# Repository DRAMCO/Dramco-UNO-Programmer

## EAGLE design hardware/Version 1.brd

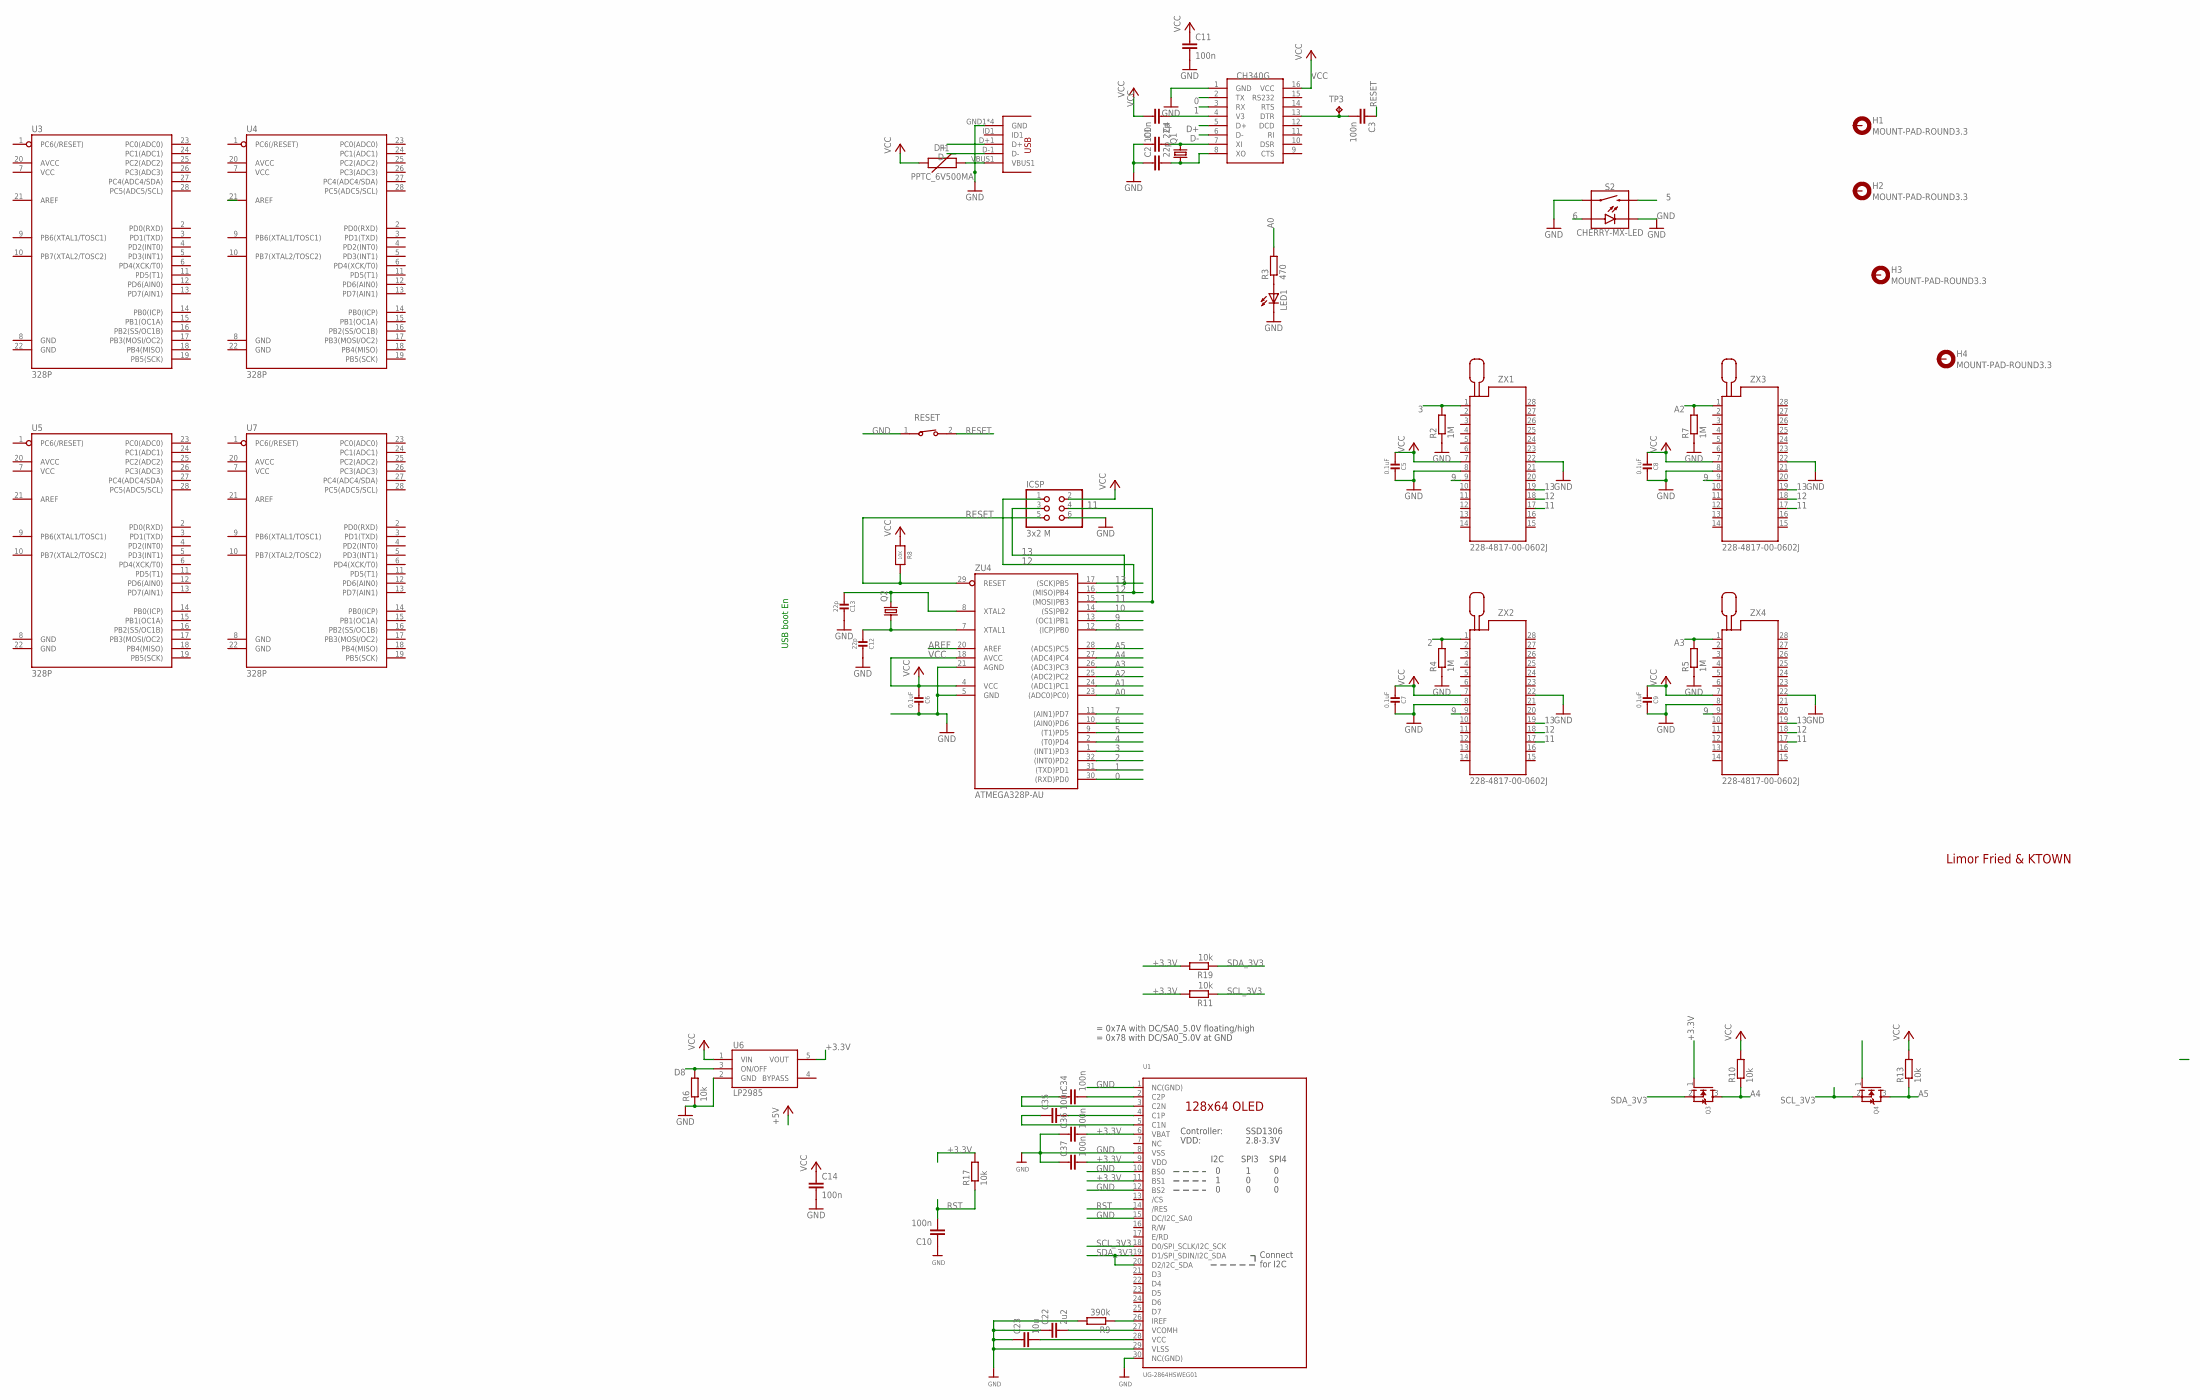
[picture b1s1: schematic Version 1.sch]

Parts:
C1, C2: 22p; C0805
C3, C4, C10, C11, C14, C34, C35, C36, C37: 100n; C0805
C5, C6, C7, C8, C9: 0.1uF; 0805-NO
C12, C13: 22p; 0805_10MGAP
C22: 2u2; C0805
C23: 10u; C0805
F1: PPTC_6V500MA; 0805
H1, H2, H3, H4: MOUNT-PAD-ROUND3.3; 3,3-PAD
ICSP: 3x2 M; 2X03_ROUND_70MIL
J1: USB-AB; USB-AB-MICRO-SMD_V02_BOSS
LED1: LEDCHIPLED_0805; CHIPLED_0805
Q1, Q2: CRYSTALHC49S; HC49/S
Q3, Q4: MOSFET-NREFLOW; SOT23
R2, R4, R5, R7: 1M; R0805
R3: 470; R0805
R6, R10, R11, R13, R17, R19: 10k; R0805
R8: 10K; _0805MP
R9: 390k; R0805
RESET: 434111043826
S2: CHERRY-MX-LED
TP3: TPTP18R; TP18R
U1: UG-2864HSWEG01; UG-2864HSWEG01_0.96IN_WRAPAROUND
U2: CH340G; SOIC16
U3, U4, U5, U7: 328P; DIP28
U6: LP2985AIM5-3.3; SOT25
ZU4: ATMEGA328P-AU; TQFP32-08
ZX1, ZX2, ZX3, ZX4: 228-4817-00-0602J

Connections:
0: U2.2 (TX), ZU4.30 ((RXD)PD0)
1: U2.3 (RX), ZU4.31 ((TXD)PD1)
2: R4.2, ZU4.32 ((INT0)PD2), ZX2.1
3: R2.2, ZU4.1 ((INT1)PD3), ZX1.1
4: ZU4.2 ((T0)PD4)
5: S2.S2, ZU4.9 ((T1)PD5)
6: S2.A, ZU4.10 ((AIN0)PD6)
7: ZU4.11 ((AIN1)PD7)
8: ZU4.12 ((ICP)PB0)
9: ZU4.13 ((OC1)PB1), ZX1.9, ZX2.9, ZX3.9, ZX4.9
10: ZU4.14 ((SS)PB2)
11: ICSP.4, ZU4.15 ((MOSI)PB3), ZX1.17, ZX2.17, ZX3.17, ZX4.17
12: ICSP.1, ZU4.16 ((MISO)PB4), ZX1.18, ZX2.18, ZX3.18, ZX4.18
13: ICSP.3, ZU4.17 ((SCK)PB5), ZX1.19, ZX2.19, ZX3.19, ZX4.19
+3.3V: C36.2, C37.2, Q3.1 (G), Q4.1 (G), R11.2, R17.2, R19.2, U1.6 (VBAT), U1.9 (VDD), U1.11 (BS1), U6.5 (VOUT)
A0: R3.2, ZU4.23 ((ADC0)PC0))
A1: ZU4.24 ((ADC1)PC1)
A2: R7.2, ZU4.25 ((ADC2)PC2), ZX3.1
A3: R5.2, ZU4.26 ((ADC3)PC3), ZX4.1
A4: Q3.3 (D), R10.1, ZU4.27 ((ADC4)PC4)
A5: Q4.3 (D), R13.1, ZU4.28 ((ADC5)PC5)
AREF: ZU4.20 (AREF)
AREF1: U4.21 (AREF)
D8: R6.2, U6.3 (ON/OFF)
D+: J1.D+1 (D+), U2.5 (D+)
D-: J1.D-1 (D-), U2.6 (D-)
GND: C1.1, C2.1, C5.1, C6.1, C7.1, C8.1, C9.1, C10.1, C11.2, C12.1, C13.1, C14.2, C22.1, C23.1, C36.1, C37.1, ICSP.6, J1.GND1 (GND), J1.P$1 (GND), J1.P$2 (GND), J1.P$3 (GND), LED1.C, R2.1, R4.1, R5.1, R6.1, R7.1, R9.2, RESET.1, S2.K (C), S2.S1, U1.1 (NC(GND)), U1.8 (VSS), U1.10 (BS0), U1.12 (BS2), U1.15 (DC/I2C_SA0), U1.29 (VLSS), U1.30 (NC(GND)), U2.1 (GND), U6.2 (GND), ZU4.5 (GND), ZU4.21 (AGND), ZX1.8, ZX1.22, ZX2.8, ZX2.22, ZX3.8, ZX3.22, ZX4.8, ZX4.22
unnamed: C1.2, Q1.2, U2.7 (XI)
unnamed: C23.2, U1.28 (VCC)
unnamed: C2.2, Q1.1, U2.8 (XO)
unnamed: C3.2, TP3.TP, U2.13 (DTR)
unnamed: C4.1, U2.4 (V3)
unnamed: LED1.A, R3.1
unnamed: F1.2, J1.VBUS1
unnamed: C34.2, U1.2 (C2P)
unnamed: C22.2, U1.27 (VCOMH)
unnamed: R9.1, U1.26 (IREF)
unnamed: C34.1, U1.3 (C2N)
unnamed: C35.2, U1.4 (C1P)
unnamed: C35.1, U1.5 (C1N)
RESET: C3.1, ICSP.5, R8.1, RESET.2, ZU4.29 (RESET)
RST: C10.2, R17.1, U1.14 (/RES)
SCL_3V3: Q4.2 (S), R11.1, U1.18 (D0/SPI_SCLK/I2C_SCK)
SDA_3V3: Q3.2 (S), R19.1, U1.19 (D1/SPI_SDIN/I2C_SDA), U1.20 (D2/I2C_SDA)
VCC: C4.2, C5.2, C6.2, C7.2, C8.2, C9.2, C11.1, C14.1, F1.1, ICSP.2, R8.2, R10.2, R13.2, U2.16 (VCC), U6.1 (VIN), ZU4.4 (VCC), ZU4.18 (AVCC), ZX1.7, ZX2.7, ZX3.7, ZX4.7
XTAL1: C12.2, Q2.1, ZU4.7 (XTAL1)
XTAL2: C13.2, Q2.2, ZU4.8 (XTAL2)

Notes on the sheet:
USB boot En
Limor Fried & KTOWN
= 0x7A with DC/SA0_5.0V floating/high
= 0x78 with DC/SA0_5.0V at GND

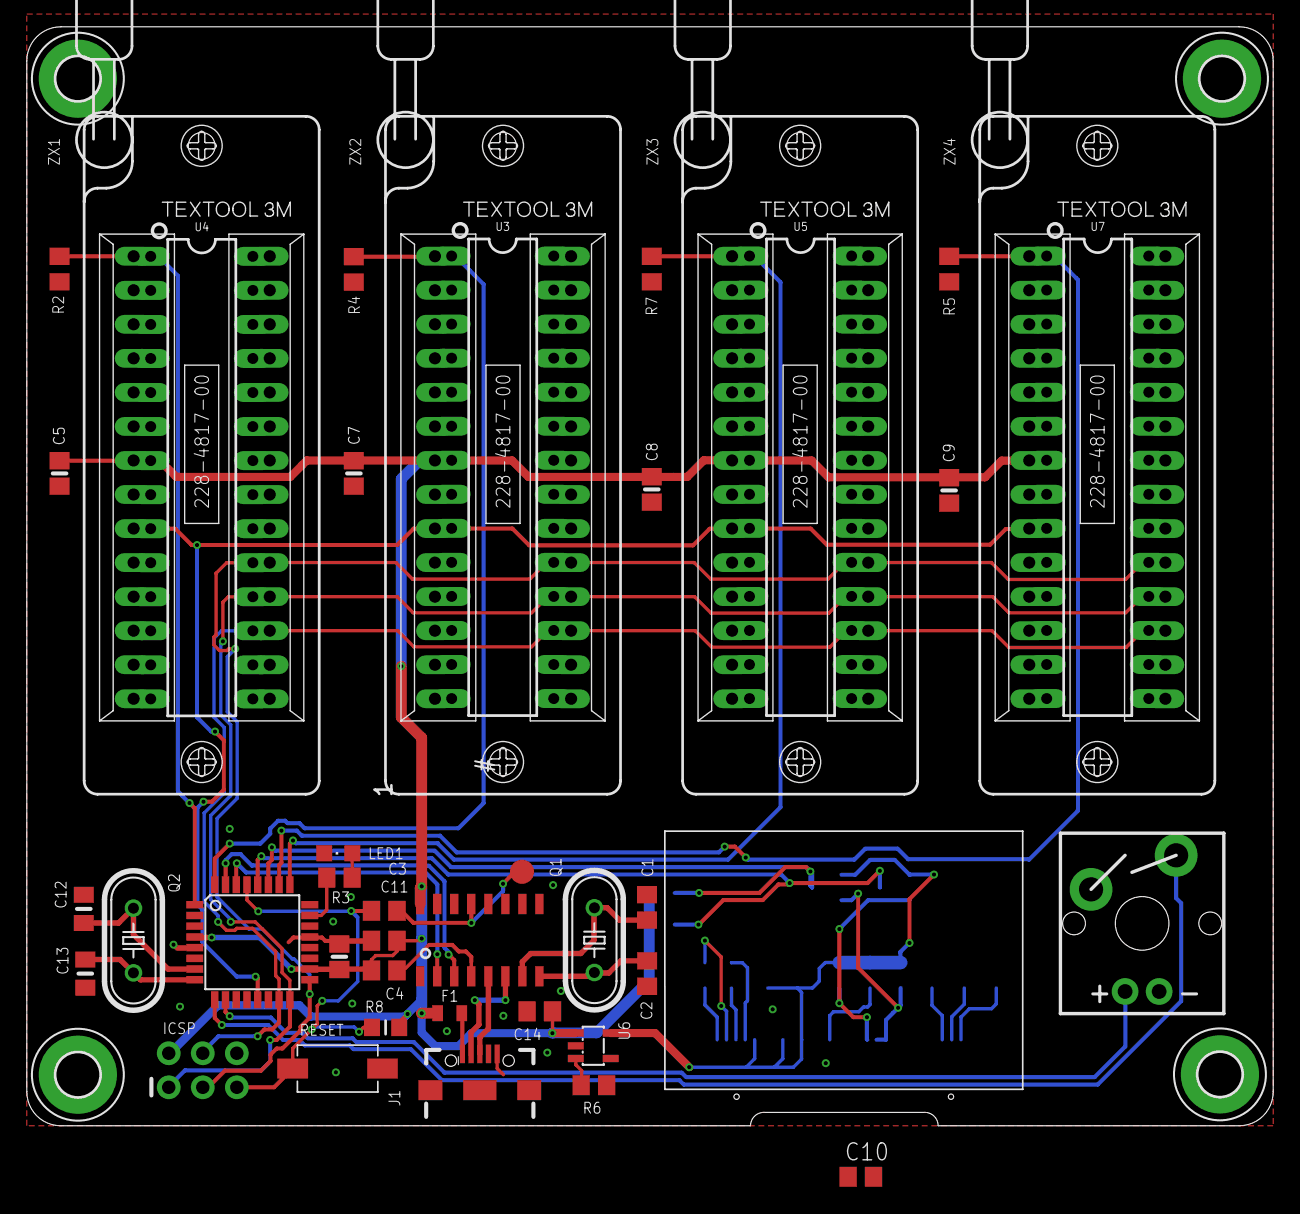
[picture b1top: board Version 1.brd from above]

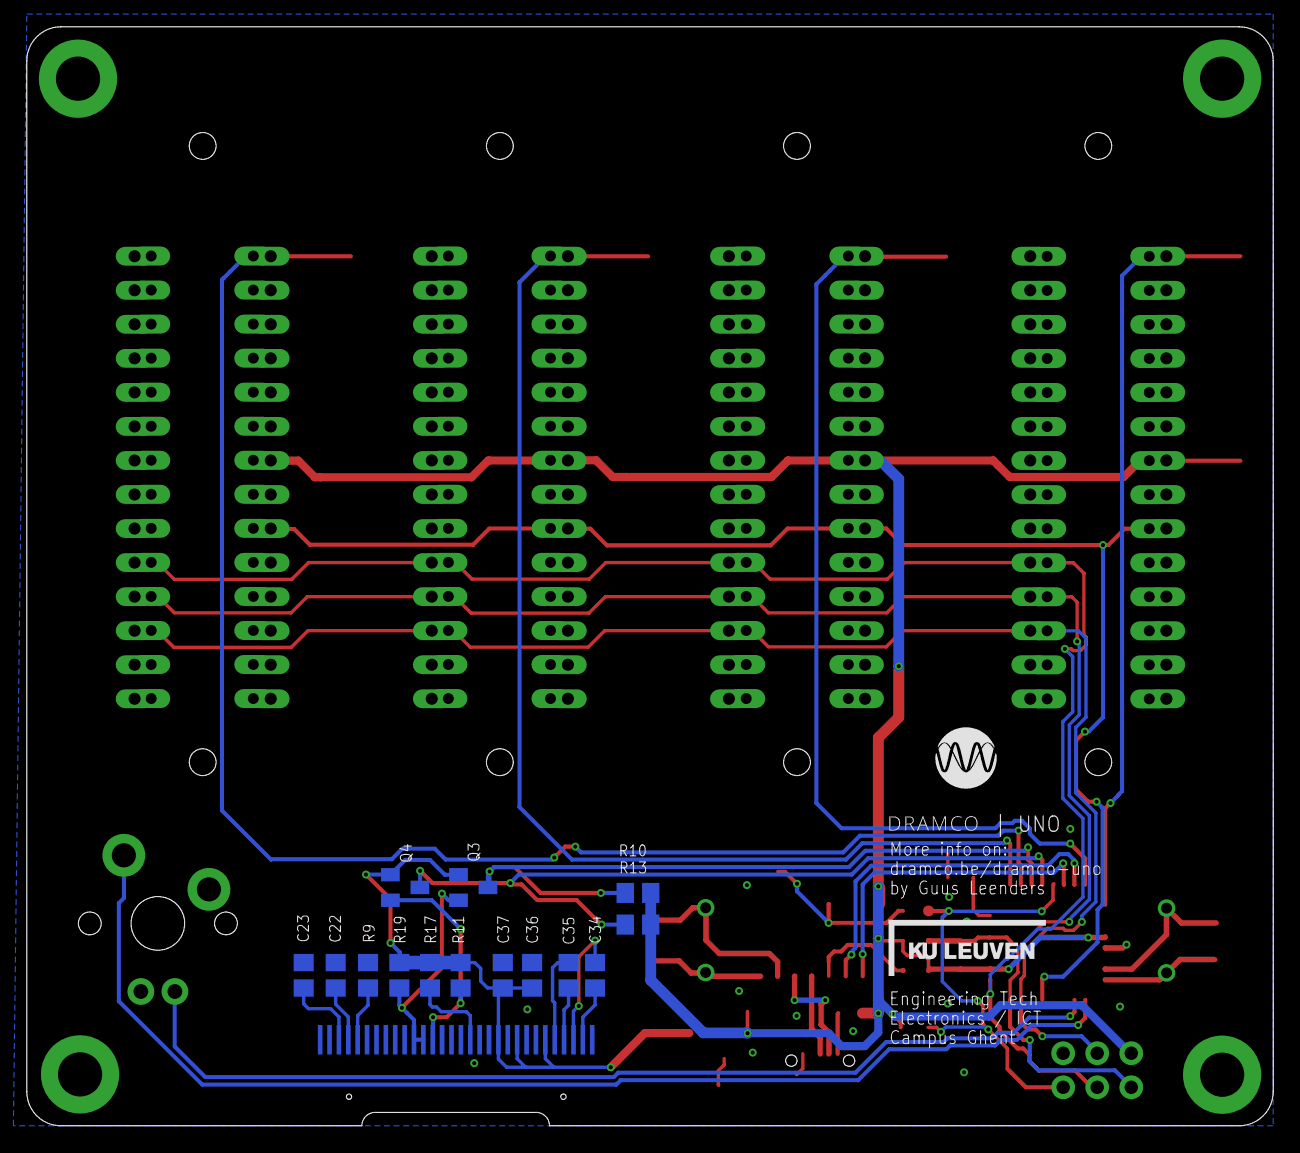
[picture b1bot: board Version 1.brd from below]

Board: 2 copper layers, 93.0 x 82.0 mm, 60 parts (14 on the bottom side), 40 nets.

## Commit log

2022-02-14 Changed led pin for Dramco Uno v2

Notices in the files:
parts and their libraries:
microbuilder: This work is placed in the public domain, and may be freely used for commercial and non-commercial work with the following conditions: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
SparkFun-Fuses: Licensing: Creative Commons ShareAlike 4.0 International - https://creativecommons.org/licenses/by-sa/4.0
